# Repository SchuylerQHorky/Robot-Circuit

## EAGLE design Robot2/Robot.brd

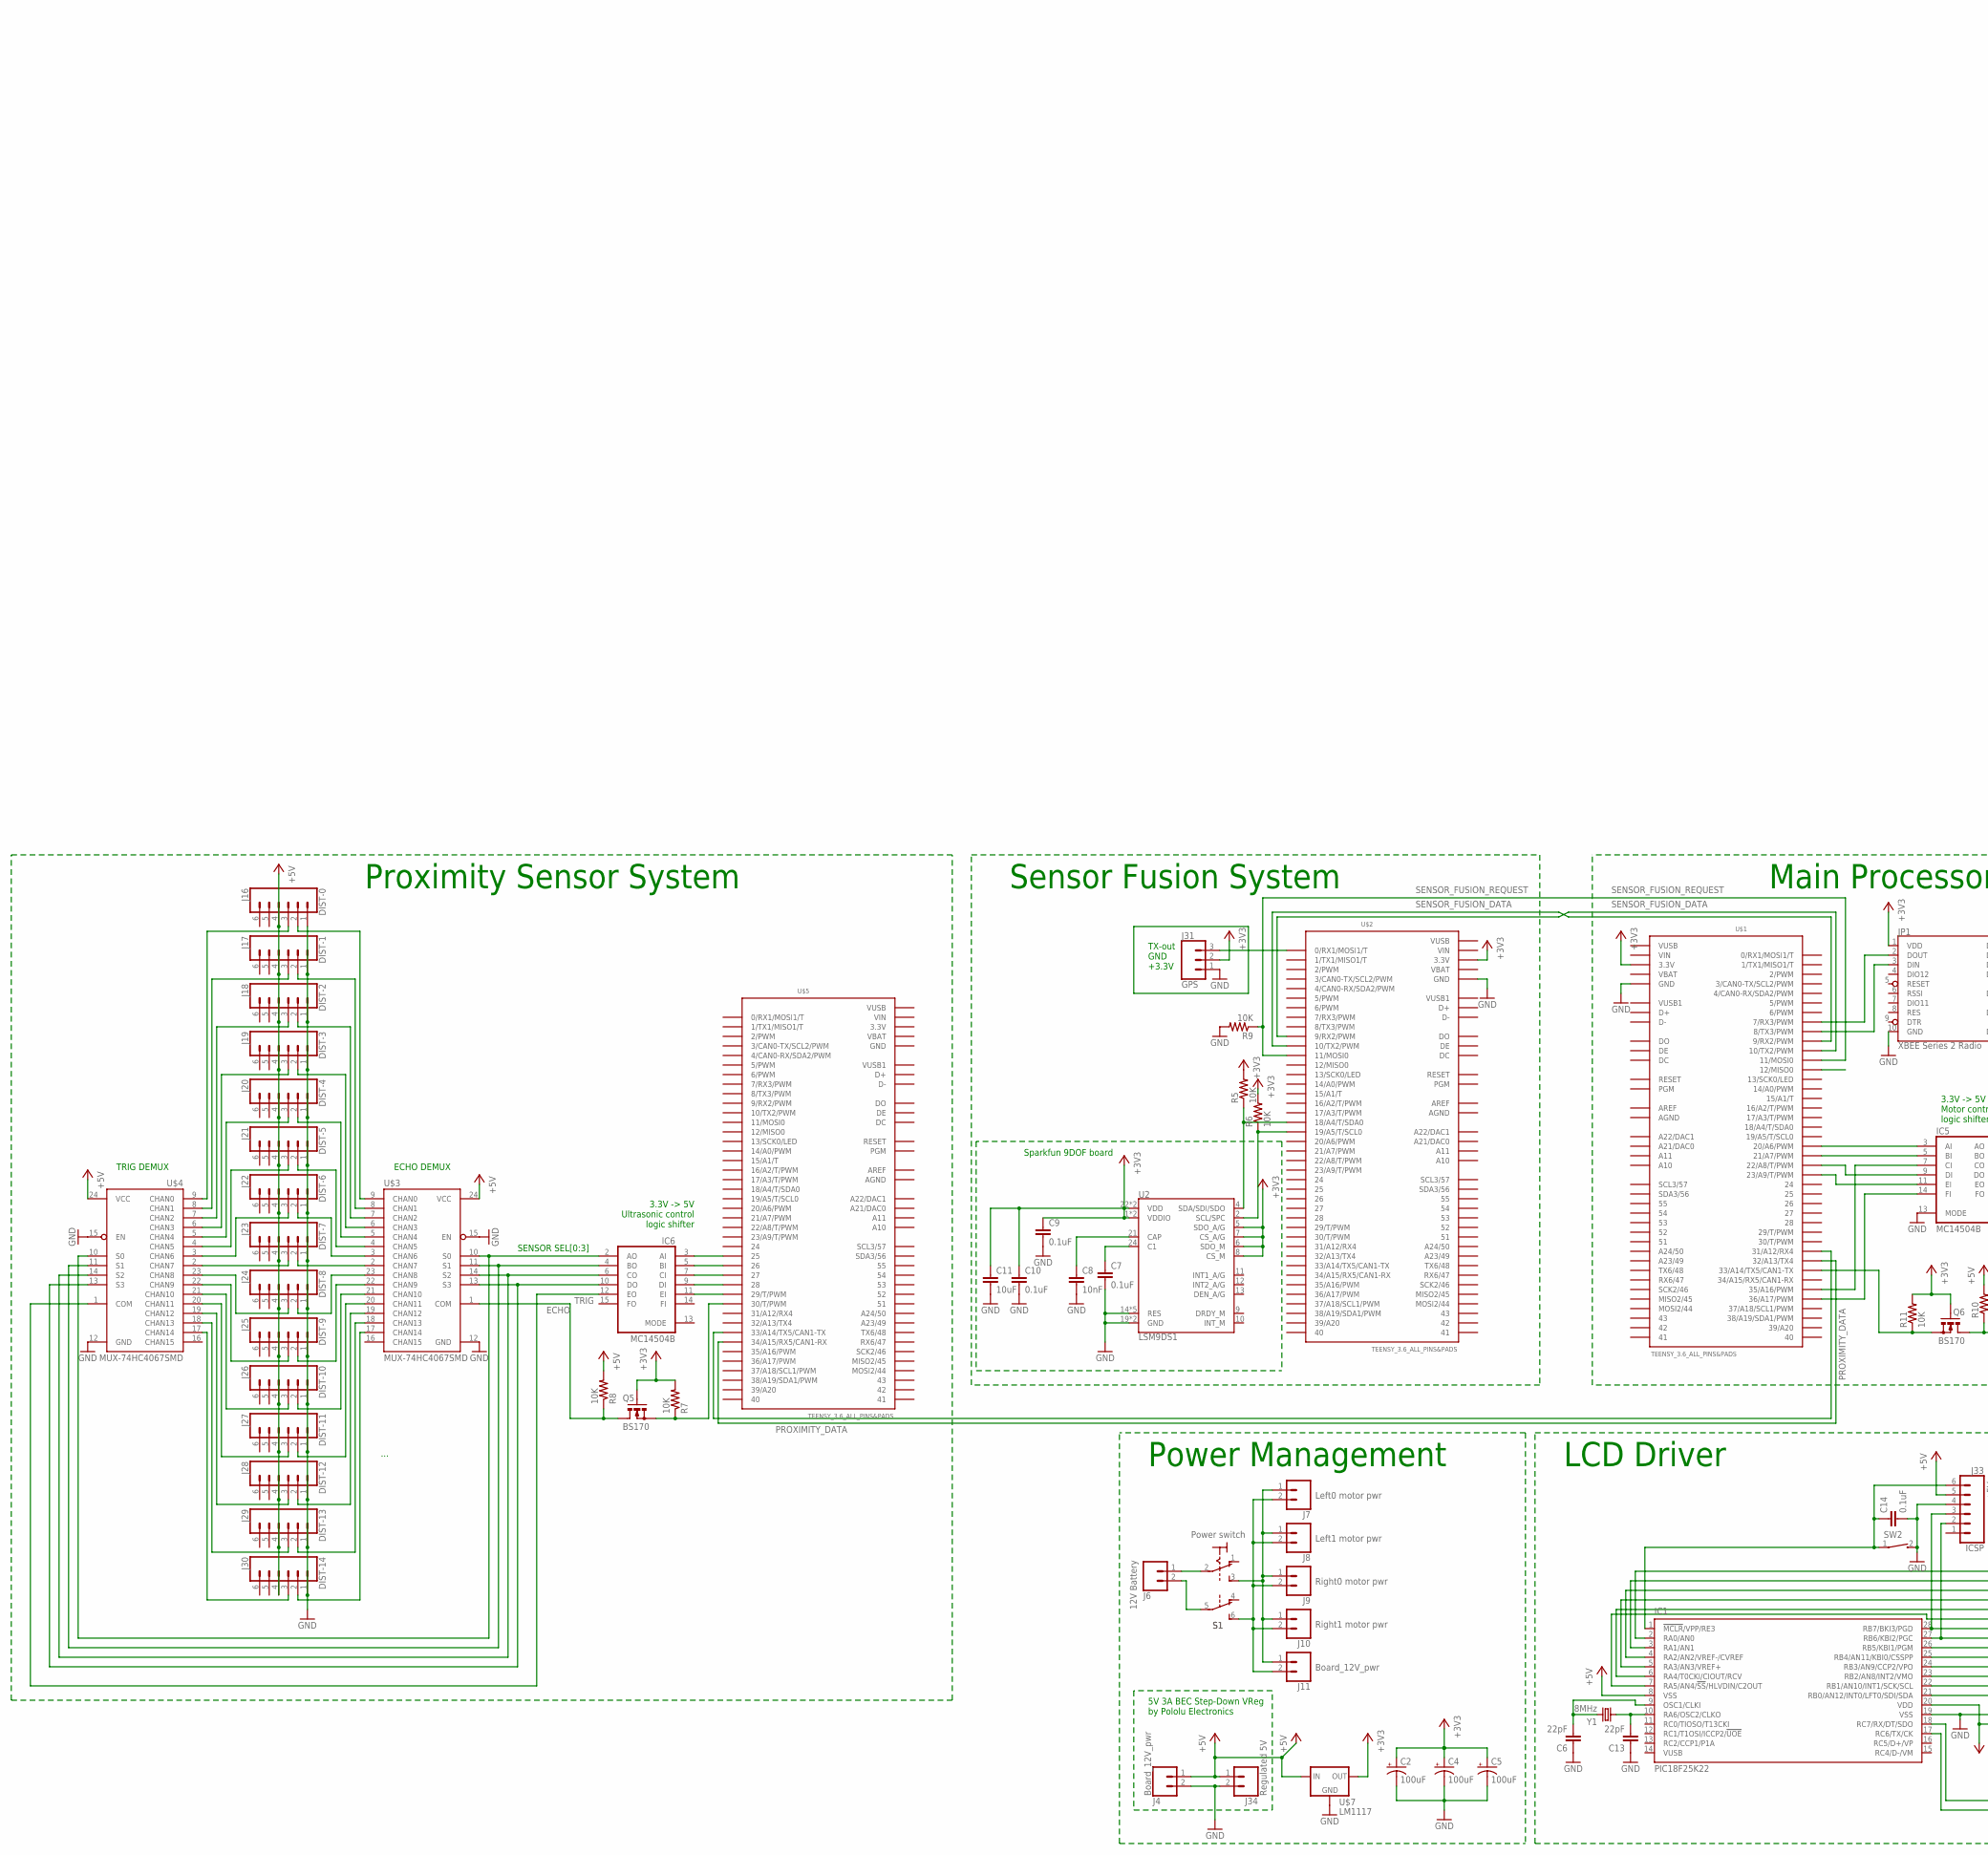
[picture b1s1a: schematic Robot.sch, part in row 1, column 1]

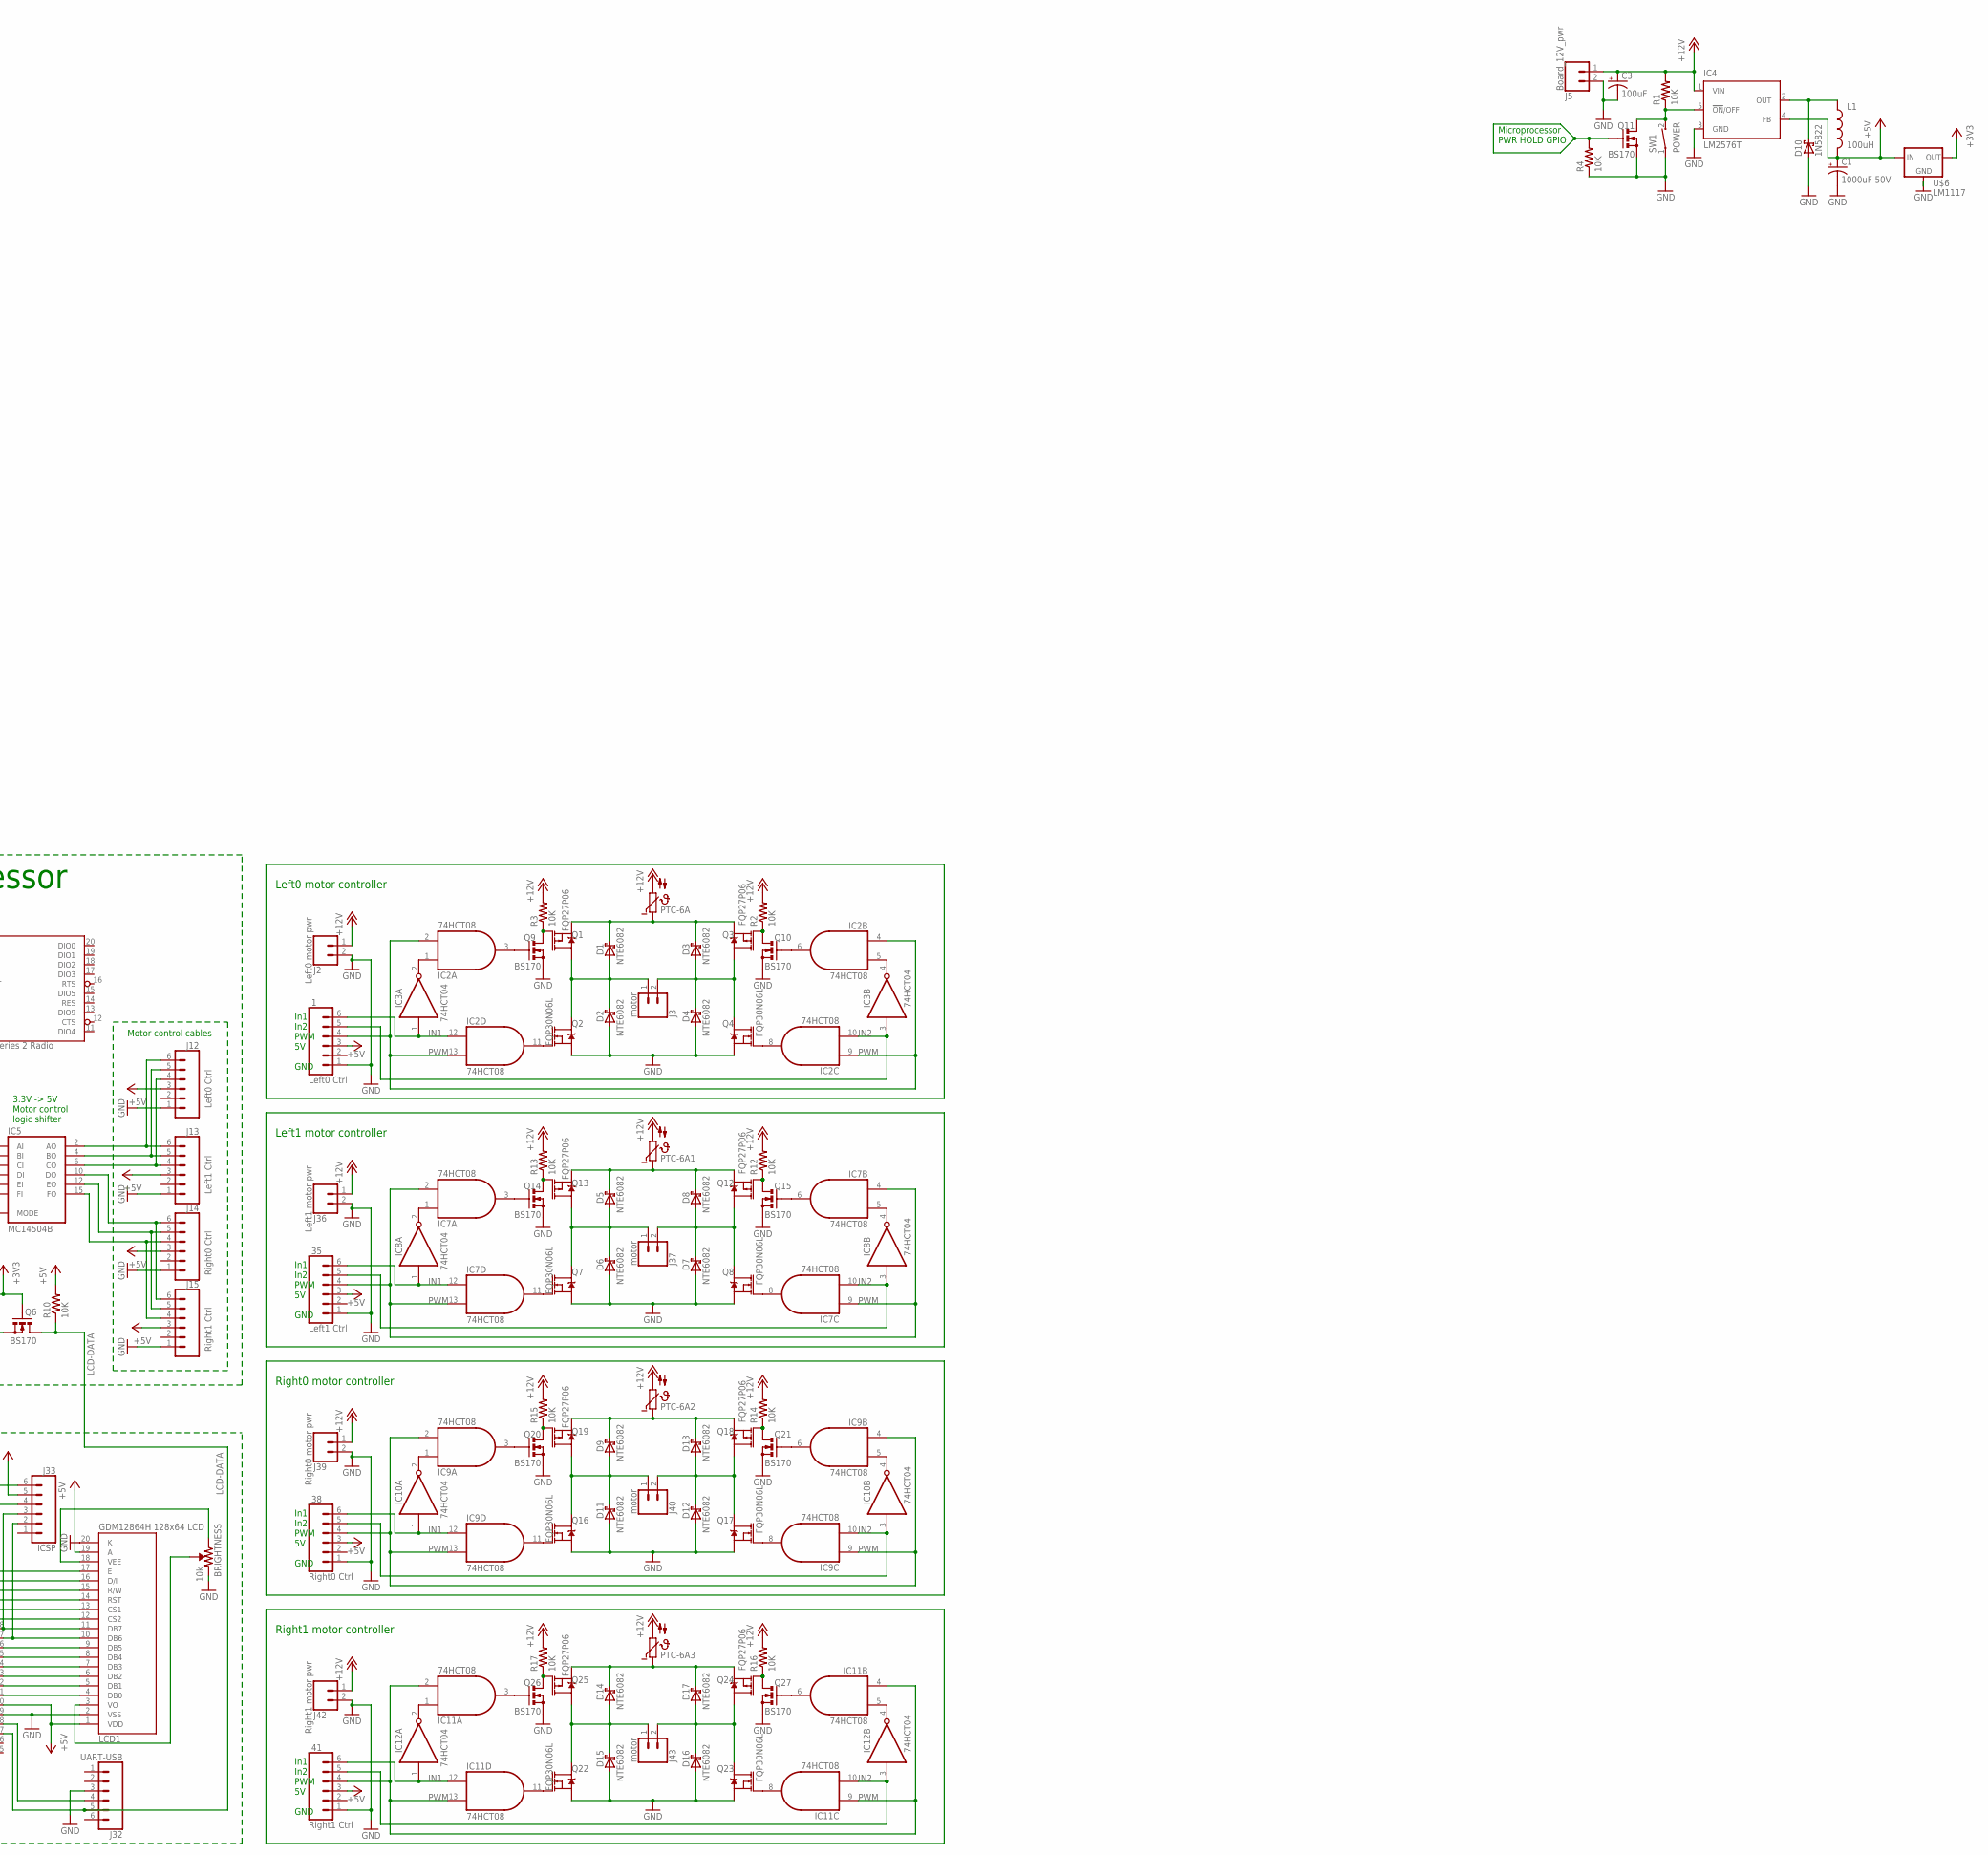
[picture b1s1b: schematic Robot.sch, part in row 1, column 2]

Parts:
BRIGHTNESS: 10k; TRIMPOT-PTH-3386U
C1: 1000uF 50V; CPOL-RADIAL-5MM-10MM-KIT
C2, C3, C4, C5: 100uF; CPOL-RADIAL-2.5MM-6.5MM
C6, C13: 22pF; CAP-PTH-SMALLEZ
C7, C9, C10, C14: 0.1uF; CAP-PTH-SMALLEZ
C8: 10nF; CAP-PTH-SMALLEZ
C11: 10uF; CAP-PTH-SMALLEZ
D1, D2, D3, D4, D5, D6, D7, D8, D9, D11, D12, D13, D14, D15, D16, D17: NTE6082; DO220S
D10: 1N5822; C4111-15
IC1: PIC18F25K22; DIL28-3
IC2, IC7, IC9, IC11: 74HCT08; DIL14
IC3, IC8, IC10, IC12: 74HCT04; DIL14
IC4: LM2576T; T05D
IC5, IC6: MC14504B; DIL16
J1, J12: Left0 Ctrl; MOLEX-1X6
J2, J7: Left0 motor pwr; SCREWTERMINAL-3.5MM-2
J3, J37, J40, J43: motor; SCREWTERMINAL-3.5MM-2
J4, J5, J11: Board_12V_pwr; SCREWTERMINAL-3.5MM-2
J6: 12V Battery; SCREWTERMINAL-3.5MM-2
J8, J36: Left1 motor pwr; SCREWTERMINAL-3.5MM-2
J9, J39: Right0 motor pwr; SCREWTERMINAL-3.5MM-2
J10, J42: Right1 motor pwr; SCREWTERMINAL-3.5MM-2
J13, J35: Left1 Ctrl; MOLEX-1X6
J14, J38: Right0 Ctrl; MOLEX-1X6
J15, J41: Right1 Ctrl; MOLEX-1X6
J16: DIST-0; MOLEX-1X6
J17: DIST-1; MOLEX-1X6
J18: DIST-2; MOLEX-1X6
J19: DIST-3; MOLEX-1X6
J20: DIST-4; MOLEX-1X6
J21: DIST-5; MOLEX-1X6
J22: DIST-6; MOLEX-1X6
J23: DIST-7; MOLEX-1X6
J24: DIST-8; MOLEX-1X6
J25: DIST-9; MOLEX-1X6
J26: DIST-10; MOLEX-1X6
J27: DIST-11; MOLEX-1X6
J28: DIST-12; MOLEX-1X6
J29: DIST-13; MOLEX-1X6
J30: DIST-14; MOLEX-1X6
J31: GPS; 1X03
J32: UART-USB; MOLEX-1X6
J33: ICSP; MOLEX-1X6
J34: Regulated 5V; SCREWTERMINAL-3.5MM-2
JP1: XBEE Series 2 Radio; XBEE
L1: 100uH; AXIAL-0.6
LCD1: GDM12864H 128x64 LCD; LCD-G12864
PTC-6A, PTC-6A1, PTC-6A2, PTC-6A3: NTC644A; N644A
Q1, Q3, Q12, Q13, Q18, Q19, Q24, Q25: FQP27P06; TO220V
Q2, Q4, Q7, Q8, Q16, Q17, Q22, Q23: FQP30N06L; TO220V
Q5, Q6, Q9, Q10, Q11, Q14, Q15, Q20, Q21, Q26, Q27: BS170; SOT54E
R1, R2, R3, R4, R5, R6, R7, R8, R9, R10, R11, R12, R13, R14, R15, R16, R17: 10K; AXIAL-0.4
S1: Power switch; M9040P2
SW1: POWER; CT10-XXXX-A2
SW2: CT10-XXXX-A2
U2: LSM9DS1; LGA-24-3.5X3
U$1, U$2, U$5: TEENSY_3.6_ALL_PINS&PADS
U$3, U$4: MUX-74HC4067SMD; SSOP24
U$6, U$7: LM1117; 78XXL
Y1: 8MHz; HC49U-V

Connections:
3.3V: U$5.3.3V, U$5.3.3V2 (3.3V), U$5.3.3V3 (3.3V), U$5.3.3V4 (3.3V)
+3V3: C2.1 (+), C4.1 (+), C5.1 (+), C9.1, C10.1, C11.1, J31.2, JP1.1 (VDD), Q5.G, Q6.G, R5.P$2 (2), R6.P$2 (2), R7.P$2 (2), R11.P$2 (2), U2.1 (VDDIO), U2.3 (VDDIO), U2.5 (SDO_A/G), U2.6 (SDO_M), U2.7 (CS_A/G), U2.8 (CS_M), U2.22 (VDD), U2.23 (VDD), U$1.3.3V, U$1.3.3V2 (3.3V), U$1.3.3V3 (3.3V), U$1.3.3V4 (3.3V), U$2.3.3V, U$2.3.3V2 (3.3V), U$2.3.3V3 (3.3V), U$2.3.3V4 (3.3V), U$6.GND (OUT), U$7.GND (OUT)
+5V: C1.+, IC1.8 (VSS), IC1.20 (VDD), IC4.4 (FB), J1.3, J4.1, J12.3, J13.3, J14.3, J15.3, J16.4, J17.4, J18.4, J19.4, J20.4, J21.4, J22.4, J23.4, J24.4, J25.4, J26.4, J27.4, J28.4, J29.4, J30.4, J33.5, J34.1, J35.3, J38.3, J41.3, L1.P$2 (2), LCD1.1 (VDD), LCD1.19 (A), R8.P$2 (2), R10.P$2 (2), U$3.24 (VCC), U$4.24 (VCC), U$6.OUT (IN), U$7.OUT (IN)
+12V: C3.1 (+), IC4.1 (VIN), J2.1, J5.1, J36.1, J39.1, J42.1, PTC-6A.2, PTC-6A1.2, PTC-6A2.2, PTC-6A3.2, R1.P$2 (2), R2.P$2 (2), R3.P$2 (2), R12.P$2 (2), R13.P$2 (2), R14.P$2 (2), R15.P$2 (2), R16.P$2 (2), R17.P$2 (2)
AGND: U$1.AGND, U$2.AGND, U$5.AGND
AREF: U$1.AREF, U$2.AREF, U$5.AREF
ECHO: Q5.D, R8.P$1 (1), U$3.1 (COM)
GND: BRIGHTNESS.1 (CCW), C1.-, C2.2 (-), C3.2 (-), C4.2 (-), C5.2 (-), C6.1, C7.2, C8.2, C9.2, C10.2, C11.2, C13.1, C14.2, D10.A, IC1.19 (VSS), IC4.3 (GND), IC5.13 (MODE), J1.1, J2.2, J4.2, J5.2, J12.1, J13.1, J14.1, J15.1, J16.1, J17.1, J18.1, J19.1, J20.1, J21.1, J22.1, J23.1, J24.1, J25.1, J26.1, J27.1, J28.1, J29.1, J30.1, J31.1, J32.3, J33.4, J34.2, J35.1, J36.2, J38.1, J39.2, J41.1, J42.2, JP1.10 (GND), LCD1.2 (VSS), LCD1.20 (K), Q9.S, Q10.S, Q11.S, Q14.S, Q15.S, Q20.S, Q21.S, Q26.S, Q27.S, R4.P$1 (1), R9.P$2 (2), SW1.1, SW2.2, U2.14 (RES), U2.15 (RES), U2.16 (RES), U2.17 (RES), U2.18 (RES), U2.19 (GND), U2.20 (GND), U$1.GND, U$1.GND1 (GND), U$1.GND2 (GND), U$1.GND3 (GND), U$1.GND4 (GND), U$1.GND5 (GND), U$1.GND6 (GND), U$2.GND, U$2.GND1 (GND), U$2.GND2 (GND), U$2.GND3 (GND), U$2.GND4 (GND), U$2.GND5 (GND), U$2.GND6 (GND), U$3.12 (GND), U$3.15 (EN), U$4.12 (GND), U$4.15 (EN), U$6.IN (GND), U$7.IN (GND)
IN1: IC2.12 (I0), IC3.1 (I), IC7.12 (I0), IC8.1 (I), IC9.12 (I0), IC10.1 (I), IC11.12 (I0), IC12.1 (I), J1.6, J35.6, J38.6, J41.6
IN2: IC2.10 (I1), IC3.3 (I), IC7.10 (I1), IC8.3 (I), IC9.10 (I1), IC10.3 (I), IC11.10 (I1), IC12.3 (I), J1.5, J35.5, J38.5, J41.5
LCD-DATA: IC1.17 (RC6/TX/CK), J32.5, Q6.D, R10.P$1 (1)
unnamed: IC2.3 (O), Q9.G
unnamed: IC2.6 (O), Q10.G
unnamed: Q6.S, R11.P$1 (1), U$1.33/A14 (33/A14/TX5/CAN1-TX)
unnamed: IC5.11 (EI), U$1.23/A9 (23/A9/T/PWM)
unnamed: Q11.G, R4.P$2 (2)
unnamed: IC5.9 (DI), U$1.22/A8 (22/A8/T/PWM)
unnamed: J19.2, U$3.6 (CHAN3)
unnamed: IC4.5 (!ON!/OFF), Q11.D, R1.P$1 (1), SW1.2
unnamed: D10.C, IC4.2 (OUT), L1.P$1 (1)
unnamed: JP1.2 (DOUT), U$1.7 (7/RX3/PWM)
unnamed: R6.P$1 (1), U2.2 (SCL/SPC), U$2.19/A5 (19/A5/T/SCL0)
unnamed: R5.P$1 (1), U2.4 (SDA/SDI/SDO), U$2.18/A4 (18/A4/T/SDA0)
unnamed: J31.3, U$2.0 (0/RX1/MOSI1/T)
unnamed: IC5.3 (AI), U$1.20/A6 (20/A6/PWM)
unnamed: J6.1, S1.2
unnamed: J6.2, S1.5
unnamed: J7.1, J8.1, J9.1, J10.1, J11.1, S1.3 (S)
unnamed: IC5.2 (AO), J12.6, J13.6
unnamed: IC1.2 (RA0/AN0), LCD1.17 (E)
unnamed: IC1.3 (RA1/AN1), LCD1.16 (D/I)
unnamed: IC1.5 (RA3/AN3/VREF+), LCD1.14 (RST)
unnamed: IC1.21 (RB0/AN12/INT0/LFT0/SDI/SDA), LCD1.4 (DB0)
unnamed: IC1.22 (RB1/AN10/INT1/SCK/SCL), LCD1.5 (DB1)
unnamed: IC1.23 (RB2/AN8/INT2/VMO), LCD1.6 (DB2)
unnamed: IC1.24 (RB3/AN9/CCP2/VPO), LCD1.7 (DB3)
unnamed: IC1.25 (RB4/AN11/KBI0/CSSPP), LCD1.8 (DB4)
unnamed: IC1.26 (RB5/KBI1/PGM), LCD1.9 (DB5)
unnamed: IC1.27 (RB6/KBI2/PGC), J33.2, LCD1.10 (DB6)
unnamed: IC1.28 (RB7/BKI3/PGD), J33.3, LCD1.11 (DB7)
unnamed: IC1.4 (RA2/AN2/VREF-/CVREF), LCD1.15 (R/W)
unnamed: IC1.6 (RA4/T0CKI/CIOUT/RCV), LCD1.13 (CS1)
unnamed: IC1.7 (RA5/AN4/!SS!/HLVDIN/C2OUT), LCD1.12 (CS2)
unnamed: D1.A, D2.C, J3.1, Q1.2 (D), Q2.2 (D)
unnamed: D3.A, D4.C, J3.2, Q3.2 (D), Q4.2 (D)
unnamed: D1.C, D3.C, PTC-6A.1, Q1.3 (S), Q3.3 (S)
unnamed: IC2.11 (O), Q2.1 (G)
unnamed: Q3.1 (G), Q10.D, R2.P$1 (1)
unnamed: D2.A, D4.A, D6.A, D7.A, D11.A, D12.A, D15.A, D16.A, IC2.7 (GND), IC3.7 (GND), IC5.8 (GND), IC6.8 (GND), IC7.7 (GND), IC8.7 (GND), IC9.7 (GND), IC10.7 (GND), IC11.7 (GND), IC12.7 (GND), Q2.3 (S), Q4.3 (S), Q7.3 (S), Q8.3 (S), Q16.3 (S), Q17.3 (S), Q22.3 (S), Q23.3 (S), U$5.GND, U$5.GND1 (GND), U$5.GND2 (GND), U$5.GND3 (GND), U$5.GND4 (GND), U$5.GND5 (GND), U$5.GND6 (GND)
unnamed: IC2.8 (O), Q4.1 (G)
unnamed: Q1.1 (G), Q9.D, R3.P$1 (1)
unnamed: J7.2, J8.2, J9.2, J10.2, J11.2, S1.6 (S)
unnamed: BRIGHTNESS.2 (WIPER), LCD1.3 (VO)
unnamed: JP1.3 (DIN), U$1.8 (8/TX3/PWM)
unnamed: BRIGHTNESS.3 (CW), LCD1.18 (VEE)
unnamed: IC5.4 (BO), J12.5, J13.5
unnamed: D5.A, D6.C, J37.1, Q7.2 (D), Q13.2 (D)
unnamed: IC2.1 (I0), IC3.2 (O)
unnamed: IC2.5 (I1), IC3.4 (O)
unnamed: U$1.10 (10/TX2/PWM), U$2.9 (9/RX2/PWM)
unnamed: IC5.6 (CO), J12.4, J13.4
unnamed: IC5.10 (DO), J14.6, J15.6
unnamed: IC5.12 (EO), J14.5, J15.5
unnamed: IC5.15 (FO), J14.4, J15.4
unnamed: J20.2, U$3.5 (CHAN4)
unnamed: J16.2, U$3.9 (CHAN0)
unnamed: J17.2, U$3.8 (CHAN1)
unnamed: J17.3, U$4.8 (CHAN1)
unnamed: J27.3, U$4.20 (CHAN11)
unnamed: J18.3, U$4.7 (CHAN2)
unnamed: J16.3, U$4.9 (CHAN0)
unnamed: J19.3, U$4.6 (CHAN3)
unnamed: J20.3, U$4.5 (CHAN4)
unnamed: J22.2, U$3.3 (CHAN6)
unnamed: J23.2, U$3.2 (CHAN7)
unnamed: J21.2, U$3.4 (CHAN5)
unnamed: J22.3, U$4.3 (CHAN6)
unnamed: J23.3, U$4.2 (CHAN7)
unnamed: J25.2, U$3.22 (CHAN9)
unnamed: J26.2, U$3.21 (CHAN10)
unnamed: J18.2, U$3.7 (CHAN2)
unnamed: J25.3, U$4.22 (CHAN9)
unnamed: J26.3, U$4.21 (CHAN10)
unnamed: J28.2, U$3.19 (CHAN12)
unnamed: J29.2, U$3.18 (CHAN13)
unnamed: IC6.2 (AO), U$3.10 (S0), U$4.10 (S0)
unnamed: J28.3, U$4.19 (CHAN12)
unnamed: J29.3, U$4.18 (CHAN13)
unnamed: J24.3, U$4.23 (CHAN8)
unnamed: J24.2, U$3.23 (CHAN8)
unnamed: IC6.4 (BO), U$3.11 (S1), U$4.11 (S1)
unnamed: J30.3, U$4.17 (CHAN14)
unnamed: J27.2, U$3.20 (CHAN11)
unnamed: IC6.6 (CO), U$3.14 (S2), U$4.14 (S2)
unnamed: IC6.10 (DO), U$3.13 (S3), U$4.13 (S3)
unnamed: J30.2, U$3.17 (CHAN14)
unnamed: Q5.S, R7.P$1 (1), U$5.30 (30/T/PWM)
unnamed: J21.3, U$4.4 (CHAN5)
unnamed: IC6.3 (AI), U$5.25
unnamed: C7.1, U2.24 (C1)
unnamed: IC6.5 (BI), U$5.26
unnamed: C8.1, U2.21 (CAP)
unnamed: IC6.7 (CI), U$5.27
unnamed: IC6.9 (DI), U$5.28
unnamed: IC6.11 (EI), U$5.29 (29/T/PWM)
unnamed: IC5.5 (BI), U$1.21/A7 (21/A7/PWM)
unnamed: IC5.7 (CI), U$1.35/A16 (35/A16/PWM)
unnamed: IC5.14 (FI), U$1.36/A17 (36/A17/PWM)
unnamed: D7.C, D8.A, J37.2, Q8.2 (D), Q12.2 (D)
unnamed: C6.2, IC1.9 (OSC1/CLKI), Y1.2
unnamed: D5.C, D8.C, PTC-6A1.1, Q12.3 (S), Q13.3 (S)
unnamed: C14.1, IC1.1 (!MCLR!/VPP/RE3), J33.6, SW2.1
unnamed: C13.2, IC1.10 (RA6/OSC2/CLKO), Y1.1
unnamed: IC1.18 (RC7/RX/DT/SDO), J32.4
unnamed: Q12.1 (G), Q15.D, R12.P$1 (1)
unnamed: Q13.1 (G), Q14.D, R13.P$1 (1)
unnamed: IC7.11 (O), Q7.1 (G)
unnamed: IC7.8 (O), Q8.1 (G)
unnamed: IC7.1 (I0), IC8.2 (O)
unnamed: IC7.5 (I1), IC8.4 (O)
unnamed: IC7.3 (O), Q14.G
unnamed: IC7.6 (O), Q15.G
unnamed: D9.A, D11.C, J40.1, Q16.2 (D), Q19.2 (D)
unnamed: D12.C, D13.A, J40.2, Q17.2 (D), Q18.2 (D)
unnamed: D9.C, D13.C, PTC-6A2.1, Q18.3 (S), Q19.3 (S)
unnamed: Q18.1 (G), Q21.D, R14.P$1 (1)
unnamed: Q19.1 (G), Q20.D, R15.P$1 (1)
unnamed: IC9.11 (O), Q16.1 (G)
unnamed: IC9.8 (O), Q17.1 (G)
unnamed: IC9.1 (I0), IC10.2 (O)
unnamed: IC9.5 (I1), IC10.4 (O)
unnamed: IC9.3 (O), Q20.G
unnamed: IC9.6 (O), Q21.G
unnamed: D14.A, D15.C, J43.1, Q22.2 (D), Q25.2 (D)
unnamed: D16.C, D17.A, J43.2, Q23.2 (D), Q24.2 (D)
unnamed: D14.C, D17.C, PTC-6A3.1, Q24.3 (S), Q25.3 (S)
unnamed: Q24.1 (G), Q27.D, R16.P$1 (1)
unnamed: Q25.1 (G), Q26.D, R17.P$1 (1)
unnamed: IC11.11 (O), Q22.1 (G)
unnamed: IC11.8 (O), Q23.1 (G)
unnamed: IC11.1 (I0), IC12.2 (O)
unnamed: IC11.5 (I1), IC12.4 (O)
unnamed: IC11.3 (O), Q26.G
unnamed: IC11.6 (O), Q27.G
unnamed: U$1.31/A12 (31/A12/RX4), U$5.33/A14 (33/A14/TX5/CAN1-TX)
PROXIMITY_DATA: U$1.32/A13 (32/A13/TX4), U$5.34/A15 (34/A15/RX5/CAN1-RX)
PWM: IC2.2 (I1), IC2.4 (I0), IC2.9 (I0), IC2.13 (I1), IC7.2 (I1), IC7.4 (I0), IC7.9 (I0), IC7.13 (I1), IC9.2 (I1), IC9.4 (I0), IC9.9 (I0), IC9.13 (I1), IC11.2 (I1), IC11.4 (I0), IC11.9 (I0), IC11.13 (I1), J1.4, J35.4, J38.4, J41.4
SENSOR_FUSION_DATA: U$1.9 (9/RX2/PWM), U$2.10 (10/TX2/PWM)
SENSOR_FUSION_REQUEST: R9.P$1 (1), U$1.11 (11/MOSI0), U$2.11 (11/MOSI0)
TRIG: IC6.12 (EO), U$4.1 (COM)
VBAT: U$1.VBAT, U$2.VBAT, U$5.VBAT
VCC: IC2.14 (VCC), IC3.14 (VCC), IC5.1 (VCC), IC6.1 (VCC), IC7.14 (VCC), IC8.14 (VCC), IC9.14 (VCC), IC10.14 (VCC), IC11.14 (VCC), IC12.14 (VCC)
VDD: IC5.16 (VDD), IC6.16 (VDD)
VIN: U$1.VIN, U$2.VIN, U$5.VIN
VUSB: U$1.VUSB, U$2.VUSB, U$5.VUSB
VUSB1: U$1.VUSB1, U$2.VUSB1, U$5.VUSB1

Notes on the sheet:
In1 In2 PWM 5V GND
Left0 motor controller
...
Sparkfun 9DOF board
TX-out GND +3.3V
ECHO DEMUX
TRIG DEMUX
Sensor Fusion System
Main Processor
3.3V -> 5V Motor control logic shifter
3.3V -> 5V Ultrasonic control logic shifter
Proximity Sensor System
SENSOR SEL[0:3]
5V 3A BEC Step-Down VReg by Pololu Electronics
LCD Driver
Motor control cables
Left1 motor controller
Right0 motor controller
Right1 motor controller
Power Management
Microprocessor PWR HOLD GPIO

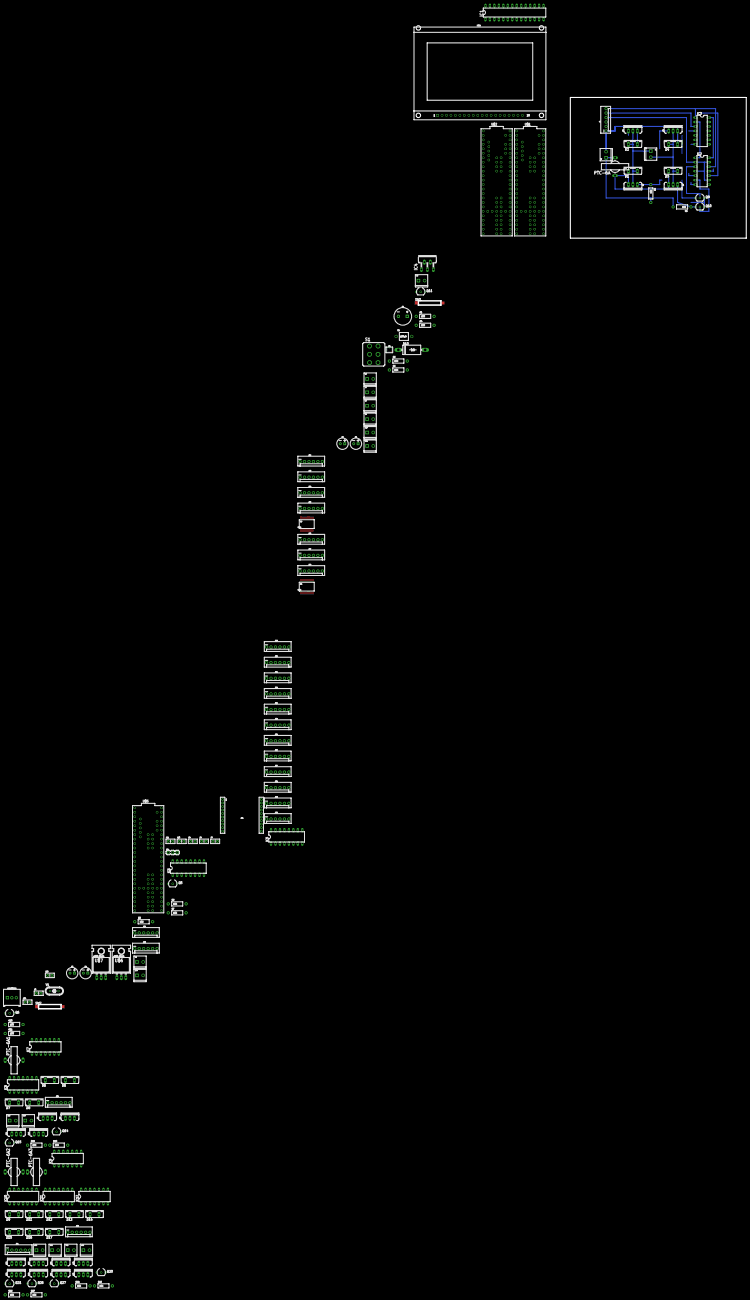
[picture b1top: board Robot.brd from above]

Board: 2 copper layers, 149 parts (0 on the bottom side), 156 nets.

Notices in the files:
parts and their libraries:
SparkFun-Connectors: Licensing: Creative Commons ShareAlike 4.0 International - https://creativecommons.org/licenses/by-sa/4.0
